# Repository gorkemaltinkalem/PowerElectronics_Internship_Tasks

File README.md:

# PowerElectronics_Internship_Tasks
LTspice ve KiCad kullanılarak, MOSFET, diyot, bobin ve kondansatör gibi ayrık (discrete) güç elektroniği bileşenleri ile bir buck (düşürücü) dönüştürücü devresinin tasarımı, analizi ve simülasyonu gerçekleştirilmiştir...

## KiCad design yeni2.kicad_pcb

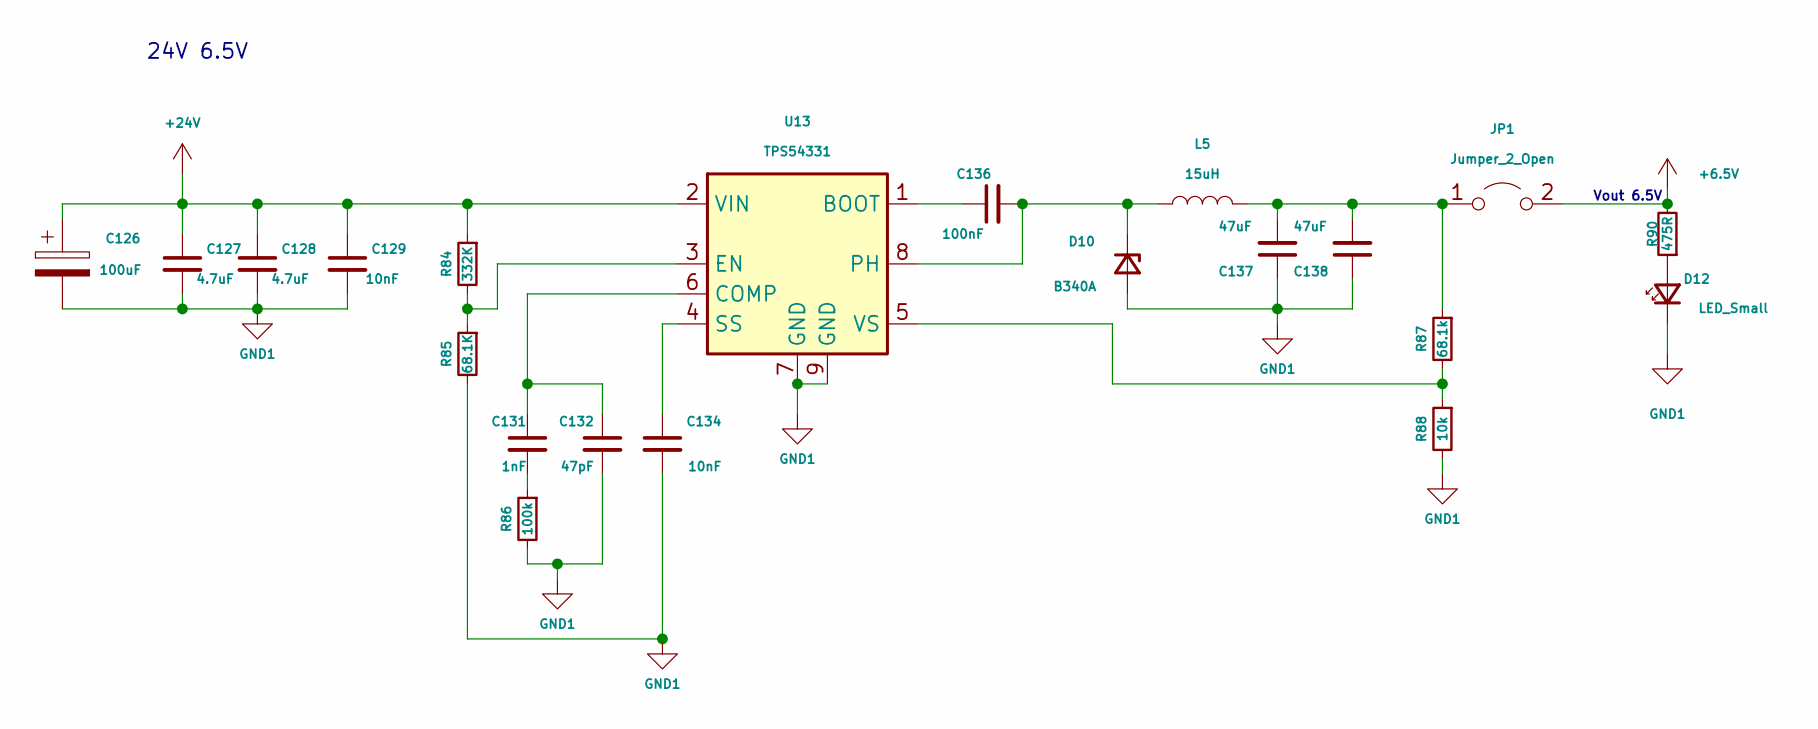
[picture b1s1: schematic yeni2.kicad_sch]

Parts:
C126: 100uF; CP_Radial_D8.0mm_P3.50mm
C127, C128: 4.7uF; C_1206_3216Metric
C129: 10nF; C_0805_2012Metric
C131: 1nF; C_0603_1608Metric
C132: 47pF; C_0603_1608Metric
C134: 10nF; C_0603_1608Metric
C136: 100nF; C_0603_1608Metric
C137, C138: 47uF; C_1206_3216Metric
D10: B340A; D_SMA
D12: LED_Small; LED_0805_2012Metric
JP1: Jumper_2_Open; TestPoint_2Pads_Pitch2.54mm_Drill0.8mm
L5: 15uH; L_12x12mm_H8mm
R84: 332K; R_0603_1608Metric
R85: 68.1K; R_0603_1608Metric
R86: 100k; R_0603_1608Metric
R87: 68.1k; R_0603_1608Metric
R88: 10k; R_0603_1608Metric
R90: 475R; R_0805_2012Metric
U13: TPS54331; SOIC-8-1EP_3.9x4.9mm_P1.27mm_EP2.514x3.2mm

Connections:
+6.5V: JP1.2 (B), R90.2
+24V: C126.1, C127.1, C128.1, C129.1, R84.1, U13.2 (VIN)
GND1: C126.2, C127.2, C128.2, C129.2, C132.2, C134.2, C137.1, C138.1, D10.2 (A), D12.1 (K), R85.2, R86.2, R88.2, U13.7 (GND), U13.9 (GND)
unnamed: C131.2, R86.1
unnamed: C136.2, D10.1 (K), L5.1, U13.8 (PH)
unnamed: D12.2 (A), R90.1
unnamed: C137.2, C138.2, JP1.1 (A), L5.2, R87.1
unnamed: C136.1, U13.1 (BOOT)
unnamed: C131.1, C132.1, U13.6 (COMP)
unnamed: R84.2, R85.1, U13.3 (EN)
unnamed: C134.1, U13.4 (SS)
unnamed: R87.2, R88.1, U13.5 (VS)

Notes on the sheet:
24V 6.5V
Vout 6.5V

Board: 2 copper layers, 21 parts (0 on the bottom side), 12 nets, no tracks yet.

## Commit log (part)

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2026-06-28 Enhance README with detailed project description
    Updated project description to include details about the design, analysis, and simulation of a buck converter circuit using discrete power electronics components.
